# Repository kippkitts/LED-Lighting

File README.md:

# LED-Lighting
LED Lighting Designs

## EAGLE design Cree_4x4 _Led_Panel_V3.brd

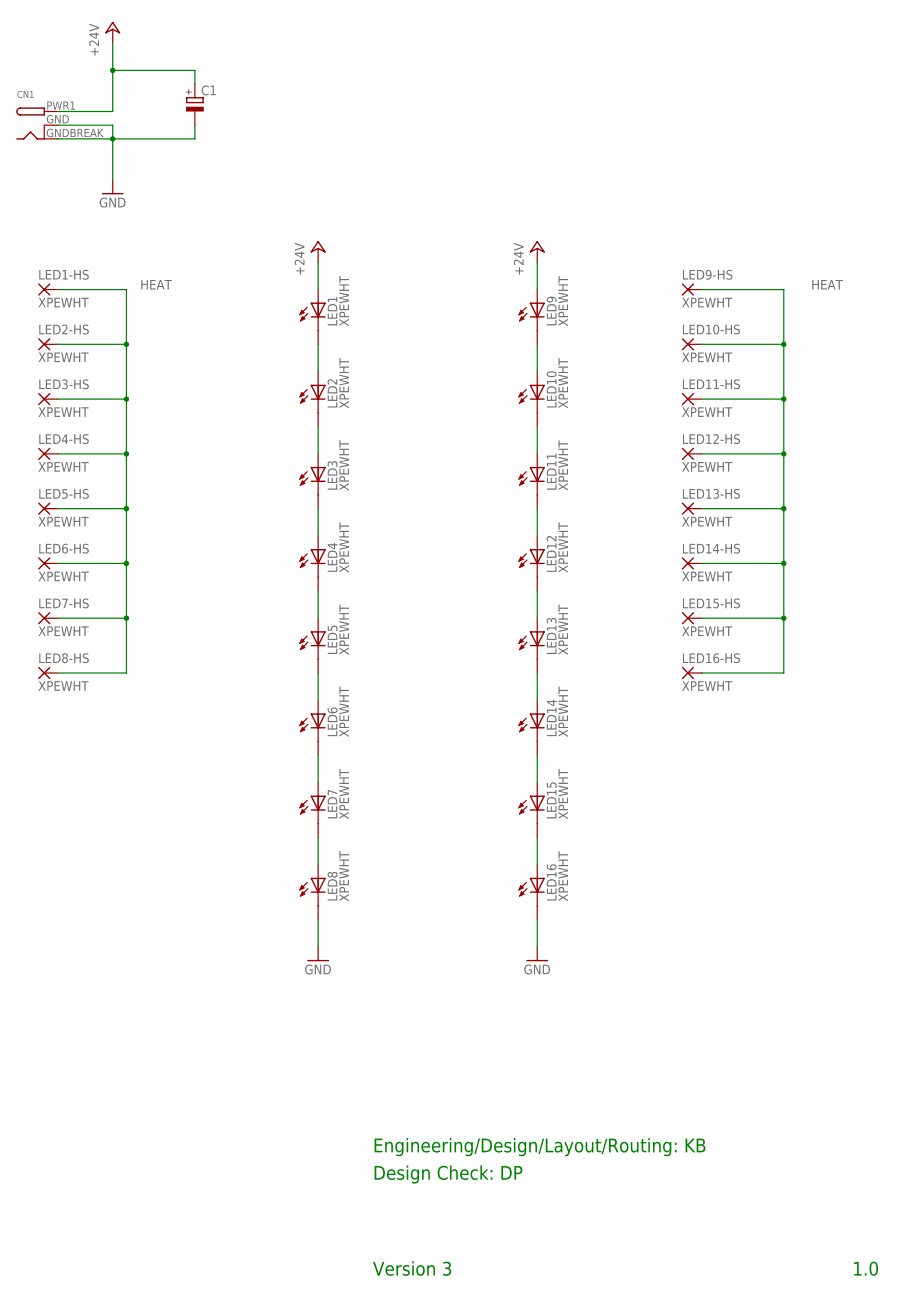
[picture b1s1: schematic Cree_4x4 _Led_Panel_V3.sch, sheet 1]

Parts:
C1: CPOL-EUSMCC; SMC_C
CN1: DCBARRELSMT; DCJACK_2MM_SMT
LED1, LED2, LED3, LED4, LED5, LED6, LED7, LED8, LED9, LED10, LED11, LED12, LED13, LED14, LED15, LED16: XPEWHT; CREE_XLAMP

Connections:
+24V: C1.+, CN1.PWR1 (PWR), LED1.A, LED9.A
GND: C1.-, CN1.GND (GNDBREAK), CN1.GNDBREAK (GND), LED8.C, LED16.C
HEAT: LED1.X, LED2.X, LED3.X, LED4.X, LED5.X, LED6.X, LED7.X, LED8.X, LED9.X, LED10.X, LED11.X, LED12.X, LED13.X, LED14.X, LED15.X, LED16.X
unnamed: LED1.C, LED2.A
unnamed: LED2.C, LED3.A
unnamed: LED3.C, LED4.A
unnamed: LED5.C, LED6.A
unnamed: LED6.C, LED7.A
unnamed: LED9.C, LED10.A
unnamed: LED10.C, LED11.A
unnamed: LED7.C, LED8.A
unnamed: LED4.C, LED5.A
unnamed: LED11.C, LED12.A
unnamed: LED15.C, LED16.A
unnamed: LED12.C, LED13.A
unnamed: LED13.C, LED14.A
unnamed: LED14.C, LED15.A

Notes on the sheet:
Engineering/Design/Layout/Routing: KB
1.0
Version 3
Design Check: DP

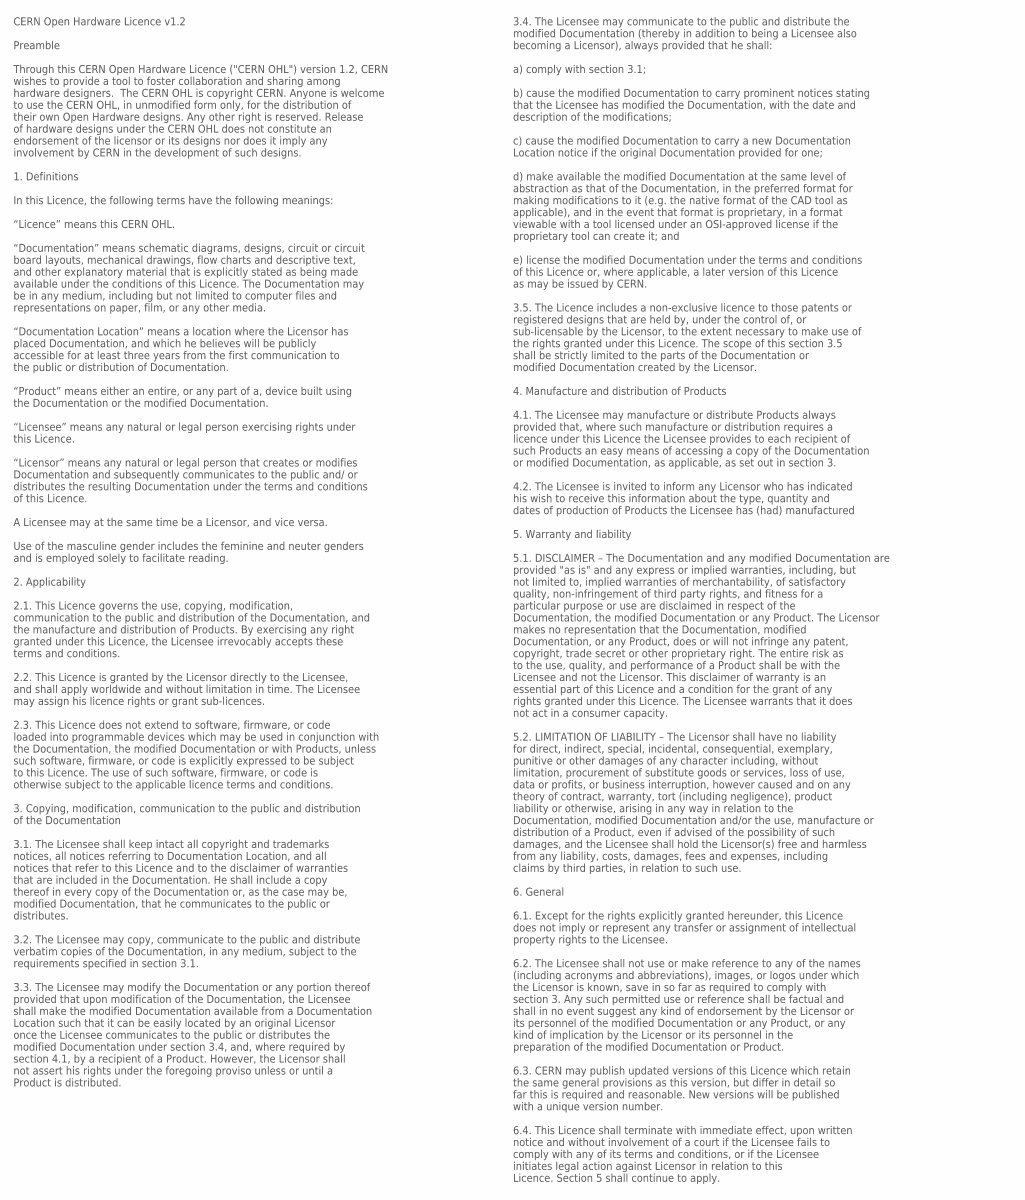
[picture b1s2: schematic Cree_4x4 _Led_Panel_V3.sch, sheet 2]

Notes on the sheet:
CERN Open Hardware Licence v1.2 Preamble Through this CERN Open Hardware Licence ("CERN OHL") version 1.2, CERN wishes to provide a tool to foster collaboration and sharing among hardware designers. The CERN OHL is copyright CERN. Anyone is welcome to use the CERN OHL, in unmodified form only, for 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
3.4. The Licensee may communicate to the public and distribute the modified Documentation (thereby in addition to being a Licensee also becoming a Licensor), always provided that he shall: a) comply with section 3.1; b) cause the modified Documentation to carry prominent notices stating that the Li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

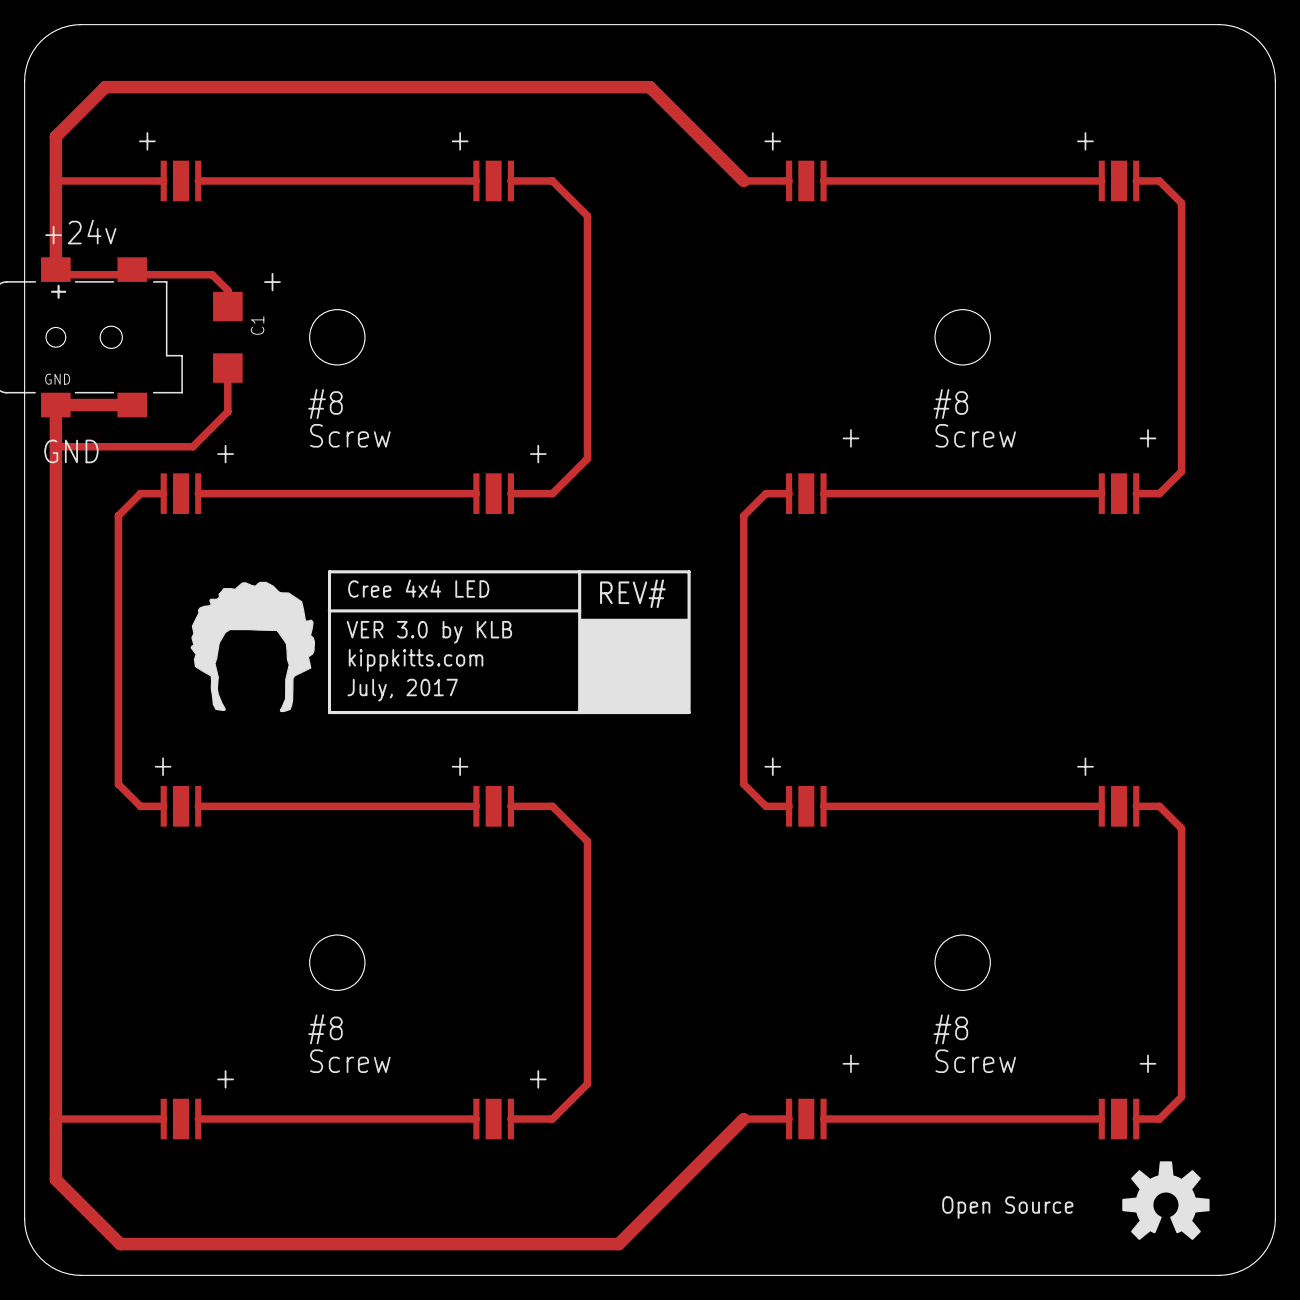
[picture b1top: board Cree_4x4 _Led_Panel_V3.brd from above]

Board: 2 copper layers, 101.6 x 101.6 mm, 22 parts (0 on the bottom side), 17 nets.

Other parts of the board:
KKLOGO: TOP_DOCU_10MM
U$1: OSHW-LOGOL; OSHW-LOGO-L
U$2: LICENSE_CERN1.2
U$3: DISCLAIMER

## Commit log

2017-07-28 Add files via upload
    Initial file upload

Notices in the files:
Cree_4x4 _Led_Panel_V3.sch:
to use the CERN OHL, in unmodified form only, for the distribution of
their own Open Hardware designs. Any other right is reserved. Release
of hardware designs under the CERN OHL does not constitute an
endorsement of the licensor or its designs nor does it imply any
available under the conditions of this Licence. The Documentation may
granted under this Licence, the Licensee irrevocably accepts these
viewable with a tool licensed under an OSI-approved license if the
proprietary tool can create it; and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
